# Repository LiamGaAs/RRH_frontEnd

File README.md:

# RRH_frontEnd
Analog part of an RRH

Pulling the repository on your computer

The following have been made on a Linux Ubuntu 18.04. 
1st, you will need to « pull » the contains of this repository to your computer. In order to achieve this, create an empty folder somewhere on your computer (desktop always the simplest).

Once created and named, open a terminal and go to your brand new folder with it.
Write the following command line : git init
 
Then, write the following command line : git pull https://github.com/LiamGaAs/RRH_frontEnd master. 
It will download all the content of the repository and store it in your newly created folder.

Installing the needed softwares :

You will need 2 : Qucs for the simulation part and Kicad for the manufacturing view part.

Installing Qucs :

Open a terminal and write the following command line : 
sudo snap install qucs-19-rg - -edge - -devmode .
Nothing else needs to be done in order to install Qucs.

Installing Kicad :

Open a terminal a write the following command line : 
sudo apt-get install kicad
Nothing else needs to be done in order to install Kicad.

See the simulation of the circuits : 

Open a terminal and go to inside the « qucs_part/simulations» folder located in your created folder.
Once there, write the following command line : 

bash all_simus_script.sh

If everything worked, 4 instances of qucs should have opened, with different file opened each time.
The 4th files names must be these ones : « F1958_matched_MAG.sch », « ampli_rf_matched_MAG.sch », « final_proto.sch » and « lna_matched_MAG.sch ».

To launch the different simulations, go at the top of each file opened and click on « simulation » and select « simulate ». 
An empty .dpl file will open. On the left, select « composants », and « diagrams » in the drop-down menu. 
Below the drop-down menu, there is a window. Click on «Cartésien », and then click in the .dpl file.  
A window will open. Double click on « S11_dB » and « S21_dB », then click « ok ». 
A graph with a red and a blue curve must have appeared.

See the manufacturing files with Kicad : 

Open a terminal and go to the « kicad_part» located in your created folder. 
Then, open a terminal and lanch the following command line : 

bash all_projects_script.sh. 

4 kicad projects should now be opened. If kicad asks you if you want to continue as kicad is already running, just answer « yes ».

The name of th 4 projects should be these ones : 

« FR4_proto.pro », « matched_lna.pro » , « match_attenuator.pro » and « matched_rf_amp.pro ».

In all these projects, in the project’s tree view,  there is one .sch file and one .kicad_pcb file.

The .sch file stands for the electronical schematic and the .kicad_pcb is the PCB file.

If you want to manufacture this PCB, you will need to produce the manufacturing files. There is 2 types needed : the gerber files and the drill files.

To achieve this, open a .kicad_pcb from any project. Then go to « file », « plot ». A window should open. 
You can choose where the ouptut files will be stored by specifying it in the « Output Directory » path. Click «on « plot » to generate the gerber files. 
Click « generate Drill file ». A new window should appear. Change nothing and click on « Generate Drill file ».

Now you can send your gerber/drill files in a .zip file to a factory in order to manufacture the PCB.

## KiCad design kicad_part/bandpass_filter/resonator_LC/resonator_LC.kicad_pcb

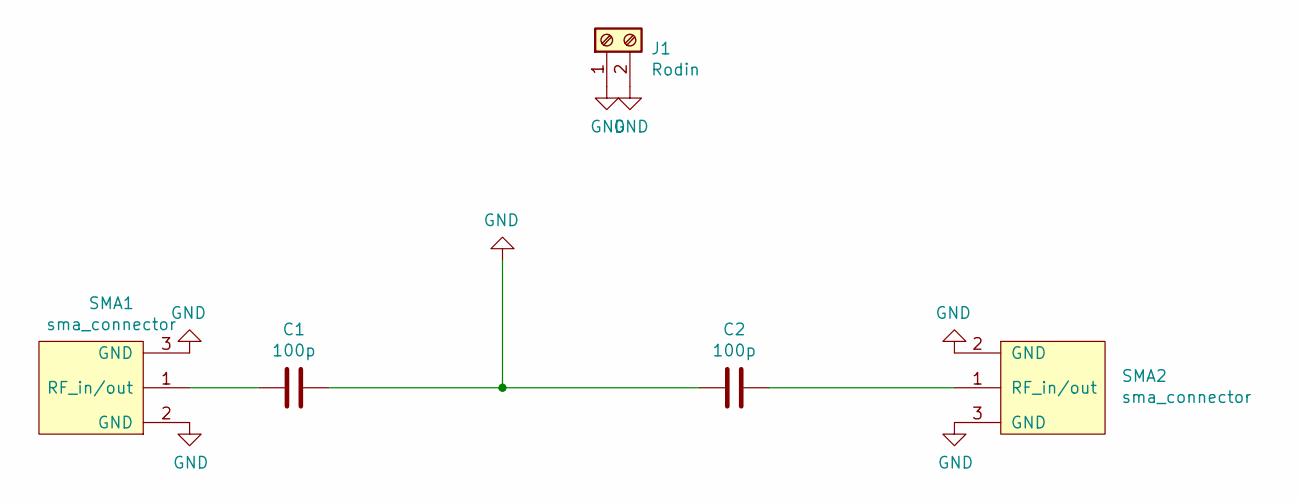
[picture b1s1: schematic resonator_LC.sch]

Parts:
C1, C2: 100p; CP_EIA-3216-10_Kemet-I_Pad1.58x1.35mm_HandSolder
J1: Rodin; PRT-08084
SMA1, SMA2: sma_connector; CONSMA003.062-G

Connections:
GND: C1.1, C2.2, J1.1, J1.2, SMA1.2 (GND), SMA1.3 (GND), SMA2.2 (GND), SMA2.3 (GND)
unnamed: C1.2, SMA1.1 (RF_in/out)
unnamed: C2.1, SMA2.1 (RF_in/out)

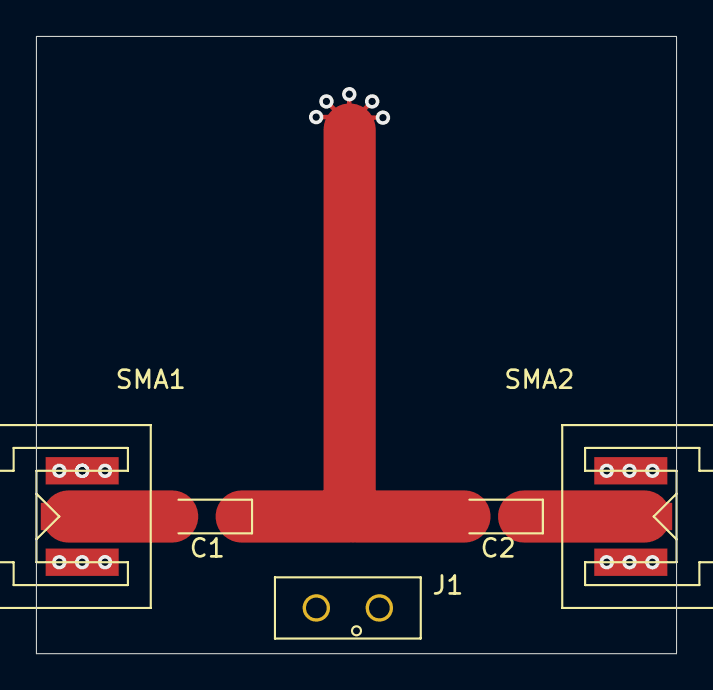
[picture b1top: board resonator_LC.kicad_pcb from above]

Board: 2 copper layers, 35.6 x 34.3 mm, 5 parts (0 on the bottom side), 3 nets.

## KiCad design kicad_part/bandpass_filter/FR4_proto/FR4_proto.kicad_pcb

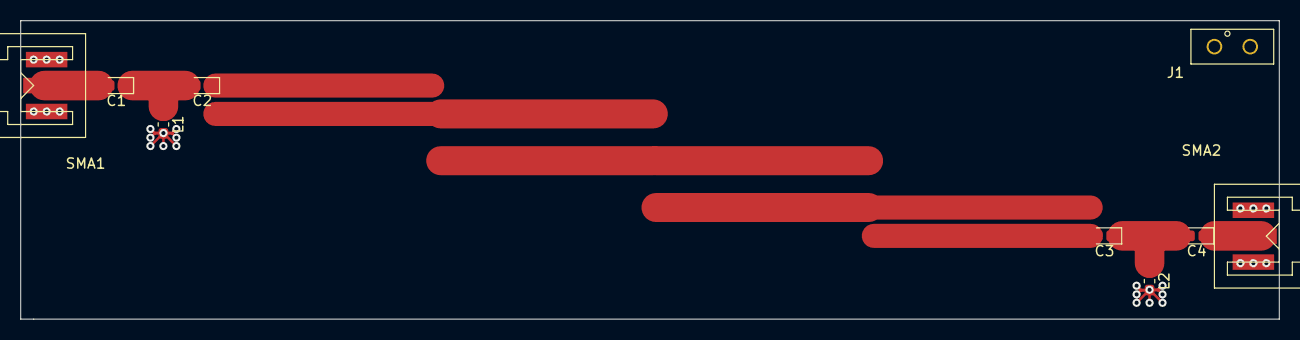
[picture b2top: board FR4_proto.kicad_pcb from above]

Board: 2 copper layers, 123.2 x 29.2 mm, 9 parts (0 on the bottom side), 5 nets.

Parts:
C1, C4: 10n; CP_EIA-1608-08_AVX-J_Pad1.25x1.05mm_HandSolder
C2, C3: 3.7p; CP_EIA-1608-08_AVX-J_Pad1.25x1.05mm_HandSolder
J1: Rodin; PRT-08084
L1, L2: 5.1n; L_0603_1608Metric_Pad1.05x0.95mm_HandSolder
SMA1, SMA2: sma_connector; CONSMA003.062-G

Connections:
GND: J1.1, J1.2, L1.2, L2.2, SMA1.2, SMA1.3, SMA2.2, SMA2.3
unnamed: C1.1, C2.2, L1.1
unnamed: C1.2, SMA1.1
unnamed: C3.1, C4.2, L2.1
unnamed: C4.1, SMA2.1

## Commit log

2019-11-22 power amplifier files
2019-11-22 added bash to open both schematic and pcb files on kicad
2019-11-22 deleted useless bash file
2019-11-22 Moved amppli_rf_matched_MAG_slug.sch from root directory to /matched_rf_amp directory
2019-11-22 adding low noise amplifier files
2019-11-22 added files about the attenuator
2019-11-25 adding bandpass filter files
2019-11-25 Rearanging project's tree view
2019-11-25 Added .sh files, so that one script opens 4 simulations
2019-11-25 Rearanging again tree view and automated the opening of the 4 kicad projects
2019-11-25 How to
2019-11-25 Corrected the readme
2019-11-26 added 2 designs to bandpass filters. Waiting to receive and testing it.
2019-11-26 understanding the way of mananging branch
2019-11-26 added kicad files and their bash files
2019-11-26 added bash files for simulation of the 2 new filters
2019-12-02 added c++ progrmam wich computes width/length/spacing of a coupled microstrip filter (Order 3 and 5 Chebyshev filter, with 0.5 dB Ripple)
2019-12-02 Removed useless comments
2019-12-02 Added a howto file to explain what is doing the c++ program
2019-12-02 Updated the howto file to explain what is doing the c++ program
2019-12-02 added a file which summarize the current state of the project
2019-12-02 Added more information about the filter's implementation in Qucs
2019-12-02 Removed Kicad and Qucs files related to the FR4_proto, as the filter does not match the specification
2019-12-02 Removed simulation files of FR4_proto (final_proto in Qucs)
2019-12-04 Added photos of filter's PCB and their simulation. Same for the attenuator
2019-12-04 Corrected names of some photos, now they can be displayed in git
2019-12-04 Updated winteriscoming.txt
2019-12-04 added 2 new filters designs
2019-12-04 added the already tested FR4_proto
